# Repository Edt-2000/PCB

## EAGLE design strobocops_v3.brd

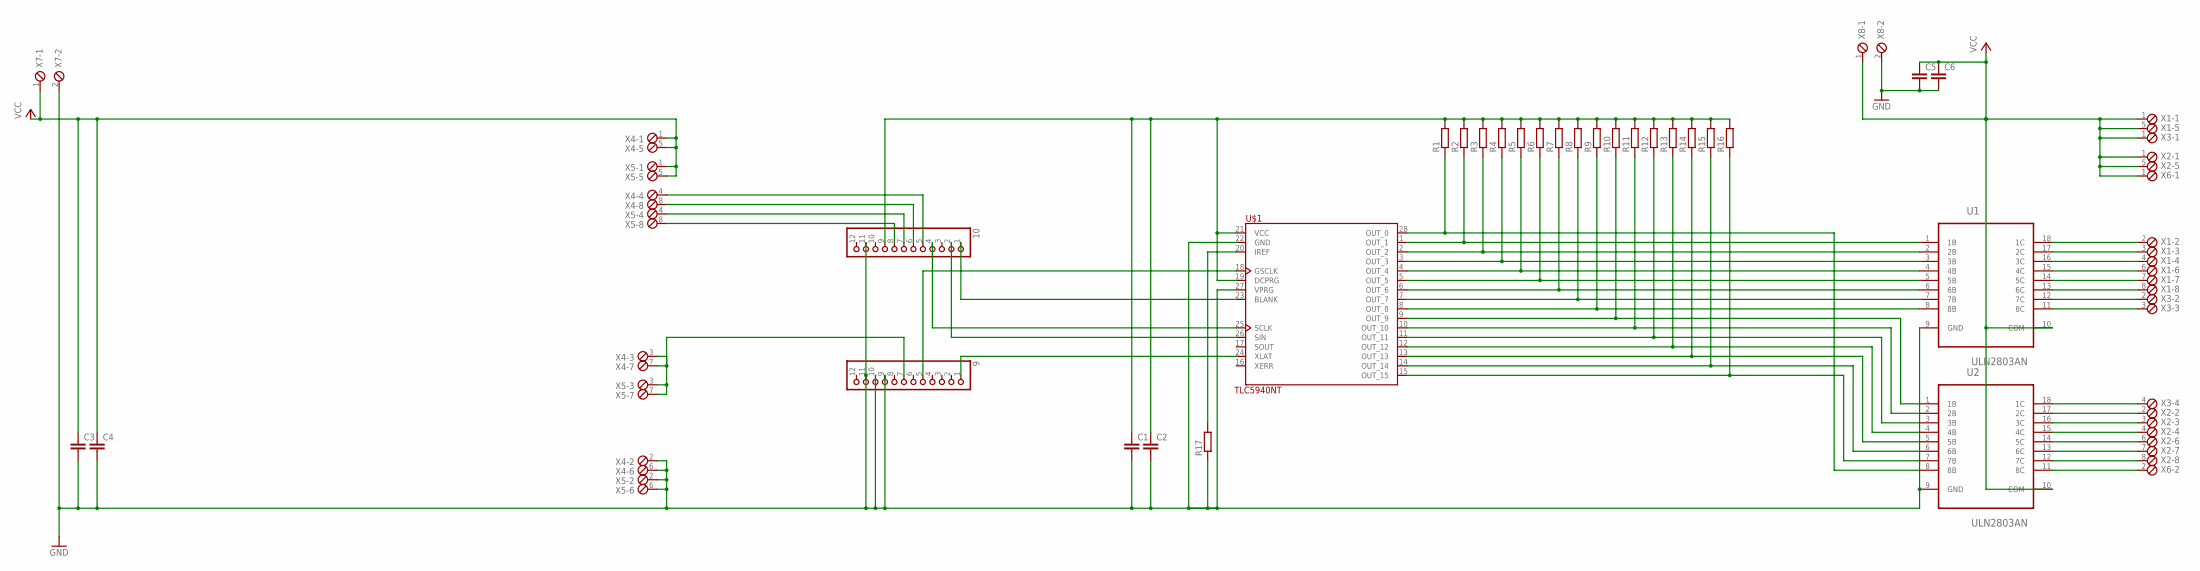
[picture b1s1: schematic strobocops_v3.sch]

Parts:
9, 10: PINHD-1X12-CB; 1X12-CB
C1, C2, C3, C4, C5, C6: C-EU050-025X075; C050-025X075
R1, R2, R3, R4, R5, R6, R7, R8, R9, R10, R11, R12, R13, R14, R15, R16, R17: R-EU_0207/2V; 0207/2V
U1, U2: ULN2803AN; DIP254P762X393-18
U$1: TLC5940NT; DIP-28
X1, X2, X4, X5: MPT8; 8POL254
X3: MPT4; 4POL254
X6, X7, X8: MPT2; 2POL254

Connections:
GND: 9.9, 9.10, 9.11, 10.11, C1.2, C2.2, C3.2, C4.2, C5.2, C6.2, R17.1, U1.9 (GND), U2.9 (GND), U$1.22 (GND), U$1.27 (VPRG), X4.2, X4.6, X5.2, X5.6, X7.2, X8.2
unnamed: 10.2, U$1.26 (SIN)
unnamed: 9.5, U$1.18 (GSCLK)
unnamed: 9.1, U$1.24 (XLAT)
unnamed: 10.1, U$1.23 (BLANK)
unnamed: 10.5, X4.4
unnamed: R2.1, U1.1 (1B), U$1.1 (OUT_1)
unnamed: R3.1, U1.2 (2B), U$1.2 (OUT_2)
unnamed: R4.1, U1.3 (3B), U$1.3 (OUT_3)
unnamed: R5.1, U1.4 (4B), U$1.4 (OUT_4)
unnamed: R6.1, U1.5 (5B), U$1.5 (OUT_5)
unnamed: R7.1, U1.6 (6B), U$1.6 (OUT_6)
unnamed: R8.1, U1.7 (7B), U$1.7 (OUT_7)
unnamed: R9.1, U1.8 (8B), U$1.8 (OUT_8)
unnamed: U1.14 (5C), X1.7
unnamed: U1.18 (1C), X1.2
unnamed: U1.17 (2C), X1.3
unnamed: U1.16 (3C), X1.4
unnamed: U1.15 (4C), X1.6
unnamed: U1.13 (6C), X1.8
unnamed: U1.12 (7C), X3.2
unnamed: U1.11 (8C), X3.3
unnamed: U2.18 (1C), X3.4
unnamed: R14.1, U2.5 (5B), U$1.13 (OUT_13)
unnamed: U2.17 (2C), X2.2
unnamed: U2.16 (3C), X2.3
unnamed: U2.15 (4C), X2.4
unnamed: U2.14 (5C), X2.6
unnamed: U2.13 (6C), X2.7
unnamed: U2.12 (7C), X2.8
unnamed: R10.1, U2.1 (1B), U$1.9 (OUT_9)
unnamed: R11.1, U2.2 (2B), U$1.10 (OUT_10)
unnamed: R12.1, U2.3 (3B), U$1.11 (OUT_11)
unnamed: R13.1, U2.4 (4B), U$1.12 (OUT_12)
unnamed: R15.1, U2.6 (6B), U$1.14 (OUT_14)
unnamed: R16.1, U2.7 (7B), U$1.15 (OUT_15)
unnamed: 9.7, X4.3, X4.7, X5.3, X5.7
unnamed: 10.6, X4.8
unnamed: 10.7, X5.4
unnamed: U2.11 (8C), X6.2
unnamed: 10.8, X5.8
unnamed: R17.2, U$1.20 (IREF)
unnamed: R1.1, U2.8 (8B), U$1.28 (OUT_0)
unnamed: 10.4, U$1.25 (SCLK)
VCC: C3.1, C4.1, X4.1, X4.5, X5.1, X5.5, X7.1
VCC_5V: 10.9, C1.1, C2.1, R1.2, R2.2, R3.2, R4.2, R5.2, R6.2, R7.2, R8.2, R9.2, R10.2, R11.2, R12.2, R13.2, R14.2, R15.2, R16.2, U$1.19 (DCPRG), U$1.21 (VCC)
VCC_12V: C5.1, C6.1, U1.10 (COM), U2.10 (COM), X1.1, X1.5, X2.1, X2.5, X3.1, X6.1, X8.1

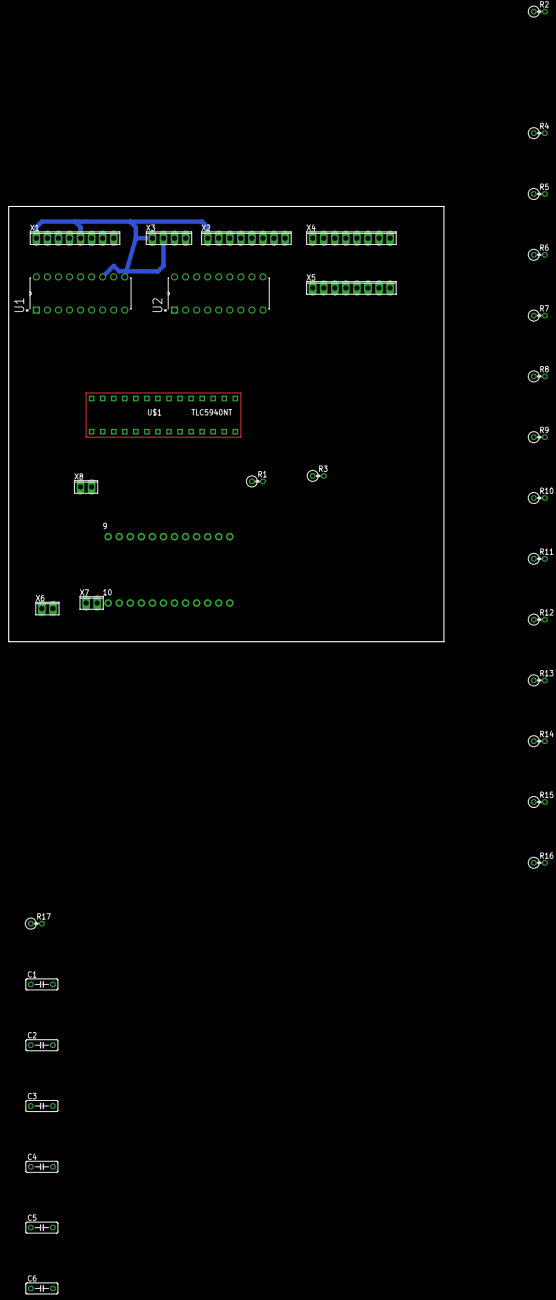
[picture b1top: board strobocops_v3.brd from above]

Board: 2 copper layers, 100.0 x 100.0 mm, 36 parts (0 on the bottom side), 47 nets.

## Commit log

2018-04-25 Initial files
